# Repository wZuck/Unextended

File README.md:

# Unextended keyboard

> Wireless NIZ development A2: [English](docs/direct-usb-A2.md) · [简体中文](docs/direct-usb-A2.zh-CN.md). ANSI 61 / BLE + USB; native nice!nano USB-C directly at the case opening, with a separate low-level carrier and revised internal V1 pocket. Not fabrication-ready. [Renders](docs/renders.md) · [Website source](website/README.md). Original ALPS project documentation follows.

Welcome to the **Unextended Keyboard** project. A 60% keyboard that targets ALPS switches and specifically the keycaps from Apple Extended Keyboards.

## Disclaimer:
I am not a case designer, this is just a personal project for me to play with 3D CAD. There are likely many best practices that are missing in this project and there are likely many improvements that can be made for better machinability. See this as a work in progress or something to get inspiration from, rather than something production ready.

**If you get these produced in PC, make sure to use threaded insers for the screws.**

## Status:
A V1 prototype has been made by PCBWay of the current V1-step model and a full wireless build have been made with a Cyber60 PCB. A mini-GB has been completed using the FE-step model by Gaoije in both PC and Aluminium and a full wired build have been made with a AEKISO60. For wireless builds I recommend the V1-model and Cyber 60 PCB. For wired builds I recommend the FE-model and either the Waffling60 Alps or the AEKISO60. MX builds can also be used in both V1 and FE cases.

I have also done a slimmer version, called Unextended Standard. This version is designed for use with M0116 or M0118 keycaps and the Unextended Standard PCB: https://github.com/4pplet/Unextended-Standard-PCB. Note: The "Standard" version of the case and PCB is not 60%. For a 60% build, use the Unextended V1 or Unextended FE and a 60% PCB (like the waffling60 alps or aekiso60).

## Keyboard Parts:
- Case
- PCB + C1 or C3 compatible daughterboard
- 3.7v single cell lipo/liion battery with a 2-pin JST PH connector (check polarity on PCB) if wireless.
- Plate
- SKUF feet
- O-ring (OD 3.5-3.55MM, Length 175-185mm)
- Cover plate for battery and daughterboard (0.6mm FR4 was used for the protos) for V1, not strictly needed.
- M2 screws for daughter board and cover plate.
- Alps switches, stabs and AEK-keycaps
- 3.7V LiPo Battery (a 3mm thick, 303759 750mAh battery was used for protos: https://www.aliexpress.com/item/33019120350.html) if wireless.

## Specs:
- V1 and FE: 60%, Standard: 55%
- Bakeneko V3 rubber worm/o-ring mount
- Compatible projects: 
  - Unextended V1 and Unextended FE: Cyber60, Waffling60 and AEKISO60 (USB-port need to be unmounted or desoldered to fit)
  - Unextended Standard FE: Unextended Standard PCB
- 5.4 degree typing angle

## Revisions:
- P1: 2021-09-20 - 3D printed concept with a bit wider bezels
- P2: 2021-11-18 - Alu CNC proto from PCB way. Slimmed down bezels and added battery cover.
- V1: 2022-01-23 - Second prototype of the case. Changed to V3 Bakeneko mounting posts and recessed and moved down the daughterboard slightly. PCBWay had issues tapping the screw holes closest to the edge for the daugheter board in P2.
- FE V1: 2022-09-17 - Reworked case by Laminar, adding a weight and removing channel for battery. This version is not intended for use with a internal battery.
- FE Standard V1: 2022-12-16 - Reworking the case to a slimmer version intended for M0116, M0118, NeXT and IIc keycaps.

## Initial 3D proto (P1):
SLA print from PCBWay
3d_print

## Initial alu proto (P2):
CNCd ALU from PCBWay

## Pics of mini GB of Unextended FE:
CNCd PC from Gaojie

## Initial proto of Unextended Standard:
Modified release for use of M0118 and M0116 keycaps. SLA Print from Gaoije, print from PCBWay also made.

<a href='https://ko-fi.com/4pplet' target='_blank'>

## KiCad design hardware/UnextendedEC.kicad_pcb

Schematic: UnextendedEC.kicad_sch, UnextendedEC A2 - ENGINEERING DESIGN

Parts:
C1, C2, C3: 100n; C_0805_2012Metric_Pad1.18x1.45mm_HandSolder
C4: 220p_C0G; C_0805_2012Metric_Pad1.18x1.45mm_HandSolder
C5: 1u; C_0805_2012Metric_Pad1.18x1.45mm_HandSolder
EC1: Esc; ecs_pad_1U_no_ring
EC2: 1; ecs_pad_1U_no_ring
EC3: 2; ecs_pad_1U_no_ring
EC4: 3; ecs_pad_1U_no_ring
EC5: 4; ecs_pad_1U_no_ring
EC6: 5; ecs_pad_1U_no_ring
EC7: 6; ecs_pad_1U_no_ring
EC8: 7; ecs_pad_1U_no_ring
EC9: 8; ecs_pad_1U_no_ring
EC10: 9; ecs_pad_1U_no_ring
EC11: 0; ecs_pad_1U_no_ring
EC12: -; ecs_pad_1U_no_ring
EC13: =; ecs_pad_1U_no_ring
EC14: Backspace; ecs_pad_1U_no_ring
EC15: Tab; ecs_pad_1U_no_ring
EC16: Q; ecs_pad_1U_no_ring
EC17: W; ecs_pad_1U_no_ring
EC18: E; ecs_pad_1U_no_ring
EC19: R; ecs_pad_1U_no_ring
EC20: T; ecs_pad_1U_no_ring
EC21: Y; ecs_pad_1U_no_ring
EC22: U; ecs_pad_1U_no_ring
EC23: I; ecs_pad_1U_no_ring
EC24: O; ecs_pad_1U_no_ring
EC25: P; ecs_pad_1U_no_ring
EC26: [; ecs_pad_1U_no_ring
EC27: ]; ecs_pad_1U_no_ring
EC28: \; ecs_pad_1U_no_ring
EC29: Caps; ecs_pad_1U_no_ring
EC30: A; ecs_pad_1U_no_ring
EC31: S; ecs_pad_1U_no_ring
EC32: D; ecs_pad_1U_no_ring
EC33: F; ecs_pad_1U_no_ring
EC34: G; ecs_pad_1U_no_ring
EC35: H; ecs_pad_1U_no_ring
EC36: J; ecs_pad_1U_no_ring
EC37: K; ecs_pad_1U_no_ring
EC38: L; ecs_pad_1U_no_ring
EC39: ;; ecs_pad_1U_no_ring
EC40: '; ecs_pad_1U_no_ring
EC41: Enter; ecs_pad_1U_no_ring
EC42: Shift; ecs_pad_1U_no_ring
EC43: Z; ecs_pad_1U_no_ring
EC44: X; ecs_pad_1U_no_ring
EC45: C; ecs_pad_1U_no_ring
EC46: V; ecs_pad_1U_no_ring
EC47: B; ecs_pad_1U_no_ring
EC48: N; ecs_pad_1U_no_ring
EC49: M; ecs_pad_1U_no_ring
EC50: ,; ecs_pad_1U_no_ring
EC51: .; ecs_pad_1U_no_ring
EC52: /; ecs_pad_1U_no_ring
EC53: RShift; ecs_pad_1U_no_ring
EC54: LCTRL; ecs_pad_1U_no_ring
EC55: LGUI; ecs_pad_1U_no_ring
EC56: LAlt; ecs_pad_1U_no_ring
EC57: Space; ecs_pad_1U_no_ring
EC58: RAlt; ecs_pad_1U_no_ring
EC59: Fn; ecs_pad_1U_no_ring
EC60: Menu; ecs_pad_1U_no_ring
EC61: RCTRL; ecs_pad_1U_no_ring
J1: JST_S2B-PH-K; Battery_PH2
J2: FH12-24S-0.5SH; Hirose_FH12-24S-0.5SH_1x24-1MP_P0.50mm_Horizontal
Q1: AO3401A; SOT-23
R1, R2, R3, R4, R5: 100; R_0805_2012Metric_Pad1.20x1.40mm_HandSolder
R10, R11, R12, R13, R14, R15, R16, R17, R18, R19, R20, R21, R22, R23, R24, R30, R33, R34, R35: 100k; R_0805_2012Metric_Pad1.20x1.40mm_HandSolder
R31, R32, R36: 1k; R_0805_2012Metric_Pad1.20x1.40mm_HandSolder
R37: 47; R_0805_2012Metric_Pad1.20x1.40mm_HandSolder
SW1: Battery_switch_pigtail; SPST_PIGTAIL_2.54
SW2: Reset_NO; RESET_2.54_TH
U2, U3: CD74HC4051M96; SOIC-16_3.9x9.9mm_P1.27mm
U4: OPA350UA; SOIC-8_3.9x4.9mm_P1.27mm

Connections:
ADC: J2.20 (ADC), R37.2 (ADC)
AFE_3V3: C3.1 (AFE_3V3), Q1.3 (D), U4.7 (V+)
AFE_GATE: Q1.1 (G), R35.1 (AFE_GATE), R36.2 (AFE_GATE)
AFE_ON_N: J2.18 (AFE_ON_N), R36.1 (AFE_ON_N)
AMP_OUT: R30.1 (AMP_OUT), R37.1 (AMP_OUT), U4.6 (OUT)
BAT_RAW: J1.1 (BAT_RAW), SW1.1 (BAT_RAW)
BAT_SW: J2.22 (BAT_SW), SW1.2 (BAT_SW)
COL0: EC1.2 (SENSE), EC15.2 (SENSE), EC29.2 (SENSE), EC54.2 (SENSE), R10.1 (COL0), U2.13 (X0)
COL1: EC2.2 (SENSE), EC42.2 (SENSE), EC55.2 (SENSE), R11.1 (COL1), U2.14 (X1)
COL2: EC3.2 (SENSE), EC16.2 (SENSE), EC30.2 (SENSE), EC43.2 (SENSE), R12.1 (COL2), U2.15 (X2)
COL3: EC4.2 (SENSE), EC17.2 (SENSE), EC31.2 (SENSE), EC44.2 (SENSE), EC56.2 (SENSE), R13.1 (COL3), U2.12 (X3)
COL4: EC5.2 (SENSE), EC18.2 (SENSE), EC32.2 (SENSE), EC45.2 (SENSE), R14.1 (COL4), U2.1 (X4)
COL5: EC6.2 (SENSE), EC19.2 (SENSE), EC33.2 (SENSE), EC46.2 (SENSE), R15.1 (COL5), U2.5 (X5)
COL6: EC7.2 (SENSE), EC20.2 (SENSE), EC34.2 (SENSE), EC47.2 (SENSE), EC57.2 (SENSE), R16.1 (COL6), U2.2 (X6)
COL7: EC8.2 (SENSE), EC21.2 (SENSE), EC35.2 (SENSE), EC48.2 (SENSE), R17.1 (COL7), U2.4 (X7)
COL8: EC9.2 (SENSE), EC22.2 (SENSE), EC36.2 (SENSE), EC49.2 (SENSE), R18.1 (COL8), U3.13 (X0)
COL9: EC10.2 (SENSE), EC23.2 (SENSE), EC37.2 (SENSE), EC50.2 (SENSE), R19.1 (COL9), U3.14 (X1)
COL10: EC11.2 (SENSE), EC24.2 (SENSE), EC38.2 (SENSE), EC51.2 (SENSE), EC58.2 (SENSE), R20.1 (COL10), U3.15 (X2)
COL11: EC12.2 (SENSE), EC25.2 (SENSE), EC39.2 (SENSE), EC52.2 (SENSE), EC59.2 (SENSE), R21.1 (COL11), U3.12 (X3)
COL12: EC13.2 (SENSE), EC26.2 (SENSE), EC40.2 (SENSE), R22.1 (COL12), U3.1 (X4)
COL13: EC27.2 (SENSE), EC41.2 (SENSE), EC53.2 (SENSE), EC60.2 (SENSE), R23.1 (COL13), U3.5 (X5)
COL14: EC14.2 (SENSE), EC28.2 (SENSE), EC61.2 (SENSE), R24.1 (COL14), U3.2 (X6)
DRAIN: J2.17 (DRAIN), R32.1 (DRAIN)
FB: R30.2 (FB), R31.1 (FB), U4.2 (IN-)
GND: C1.2 (GND), C2.2 (GND), C3.2 (GND), C4.2 (GND), C5.2 (GND), EC1.3 (GUARD), EC2.3 (GUARD), EC3.3 (GUARD), EC4.3 (GUARD), EC5.3 (GUARD), EC6.3 (GUARD), EC7.3 (GUARD), EC8.3 (GUARD), EC9.3 (GUARD), EC10.3 (GUARD), EC11.3 (GUARD), EC12.3 (GUARD), EC13.3 (GUARD), EC14.3 (GUARD), EC15.3 (GUARD), EC16.3 (GUARD), EC17.3 (GUARD), EC18.3 (GUARD), EC19.3 (GUARD), EC20.3 (GUARD), EC21.3 (GUARD), EC22.3 (GUARD), EC23.3 (GUARD), EC24.3 (GUARD), EC25.3 (GUARD), EC26.3 (GUARD), EC27.3 (GUARD), EC28.3 (GUARD), EC29.3 (GUARD), EC30.3 (GUARD), EC31.3 (GUARD), EC32.3 (GUARD), EC33.3 (GUARD), EC34.3 (GUARD), EC35.3 (GUARD), EC36.3 (GUARD), EC37.3 (GUARD), EC38.3 (GUARD), EC39.3 (GUARD), EC40.3 (GUARD), EC41.3 (GUARD), EC42.3 (GUARD), EC43.3 (GUARD), EC44.3 (GUARD), EC45.3 (GUARD), EC46.3 (GUARD), EC47.3 (GUARD), EC48.3 (GUARD), EC49.3 (GUARD), EC50.3 (GUARD), EC51.3 (GUARD), EC52.3 (GUARD), EC53.3 (GUARD), EC54.3 (GUARD), EC55.3 (GUARD), EC56.3 (GUARD), EC57.3 (GUARD), EC58.3 (GUARD), EC59.3 (GUARD), EC60.3 (GUARD), EC61.3 (GUARD), J1.2 (GND), J2.1 (GND), J2.2 (GND), J2.4 (GND), J2.10 (GND), J2.16 (GND), J2.19 (GND), J2.21 (GND), J2.24 (GND), R10.2 (GND), R11.2 (GND), R12.2 (GND), R13.2 (GND), R14.2 (GND), R15.2 (GND), R16.2 (GND), R17.2 (GND), R18.2 (GND), R19.2 (GND), R20.2 (GND), R21.2 (GND), R22.2 (GND), R23.2 (GND), R24.2 (GND), R31.2 (GND), SW2.2 (GND), U2.7 (VEE), U2.8 (GND), U3.4 (X7), U3.7 (VEE), U3.8 (GND), U4.4 (V-)
MUX0_INH: J2.14 (MUX0_INH), R33.1 (MUX0_INH), U2.6 (INH)
MUX1_INH: J2.15 (MUX1_INH), R34.1 (MUX1_INH), U3.6 (INH)
MUX_A: J2.11 (MUX_A), U2.11 (A), U3.11 (A)
MUX_B: J2.12 (MUX_B), U2.10 (B), U3.10 (B)
MUX_C: J2.13 (MUX_C), U2.9 (C), U3.9 (C)
RESET: J2.23 (RESET), SW2.1 (RESET)
ROW0: EC1.1 (DRIVE), EC2.1 (DRIVE), EC3.1 (DRIVE), EC4.1 (DRIVE), EC5.1 (DRIVE), EC6.1 (DRIVE), EC7.1 (DRIVE), EC8.1 (DRIVE), EC9.1 (DRIVE), EC10.1 (DRIVE), EC11.1 (DRIVE), EC12.1 (DRIVE), EC13.1 (DRIVE), EC14.1 (DRIVE), R1.2 (ROW0)
ROW1: EC15.1 (DRIVE), EC16.1 (DRIVE), EC17.1 (DRIVE), EC18.1 (DRIVE), EC19.1 (DRIVE), EC20.1 (DRIVE), EC21.1 (DRIVE), EC22.1 (DRIVE), EC23.1 (DRIVE), EC24.1 (DRIVE), EC25.1 (DRIVE), EC26.1 (DRIVE), EC27.1 (DRIVE), EC28.1 (DRIVE), R2.2 (ROW1)
ROW2: EC29.1 (DRIVE), EC30.1 (DRIVE), EC31.1 (DRIVE), EC32.1 (DRIVE), EC33.1 (DRIVE), EC34.1 (DRIVE), EC35.1 (DRIVE), EC36.1 (DRIVE), EC37.1 (DRIVE), EC38.1 (DRIVE), EC39.1 (DRIVE), EC40.1 (DRIVE), EC41.1 (DRIVE), R3.2 (ROW2)
ROW3: EC42.1 (DRIVE), EC43.1 (DRIVE), EC44.1 (DRIVE), EC45.1 (DRIVE), EC46.1 (DRIVE), EC47.1 (DRIVE), EC48.1 (DRIVE), EC49.1 (DRIVE), EC50.1 (DRIVE), EC51.1 (DRIVE), EC52.1 (DRIVE), EC53.1 (DRIVE), R4.2 (ROW3)
ROW4: EC54.1 (DRIVE), EC55.1 (DRIVE), EC56.1 (DRIVE), EC57.1 (DRIVE), EC58.1 (DRIVE), EC59.1 (DRIVE), EC60.1 (DRIVE), EC61.1 (DRIVE), R5.2 (ROW4)
ROW_DRV0: J2.5 (ROW_DRV0), R1.1 (ROW_DRV0)
ROW_DRV1: J2.6 (ROW_DRV1), R2.1 (ROW_DRV1)
ROW_DRV2: J2.7 (ROW_DRV2), R3.1 (ROW_DRV2)
ROW_DRV3: J2.8 (ROW_DRV3), R4.1 (ROW_DRV3)
ROW_DRV4: J2.9 (ROW_DRV4), R5.1 (ROW_DRV4)
SENSE: C4.1 (SENSE), R32.2 (SENSE), U2.3 (COM), U3.3 (COM), U4.3 (IN+)
VCC: C1.1 (VCC), C2.1 (VCC), C5.1 (VCC), J2.3 (VCC), Q1.2 (S), R33.2 (VCC), R34.2 (VCC), R35.2 (VCC), U2.16 (VCC), U3.16 (VCC)

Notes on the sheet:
UnextendedEC A2 | NiZ EC + ANSI 6.25u + nice!nano v2 | ENGINEERING PROTOTYPE
Native nice!nano USB-C is the external port. J2 carries no USB, VBUS or high-impedance SENSE.
U2/U3: only one INH low at a time. U4 gain 101. DRAIN goes through R32 to SENSE. Q1 gates U4 only.
SW1/SW2 are 2.54mm solder-hole harnesses. No external 5V connection to U1 BATTERY+.
EC electrodes: logical row = physical row; column = floor(x_u + width_u/2), including empty column bins.

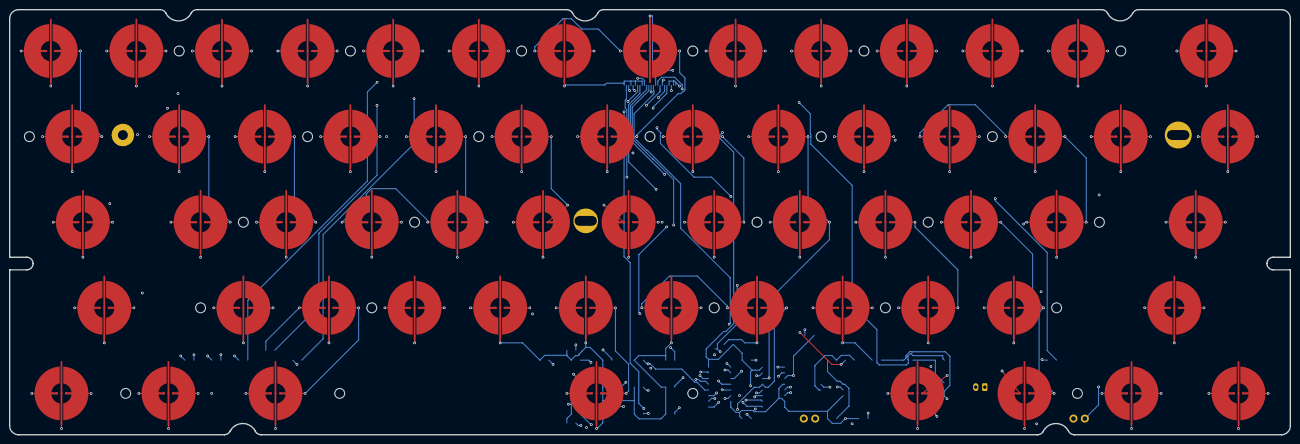
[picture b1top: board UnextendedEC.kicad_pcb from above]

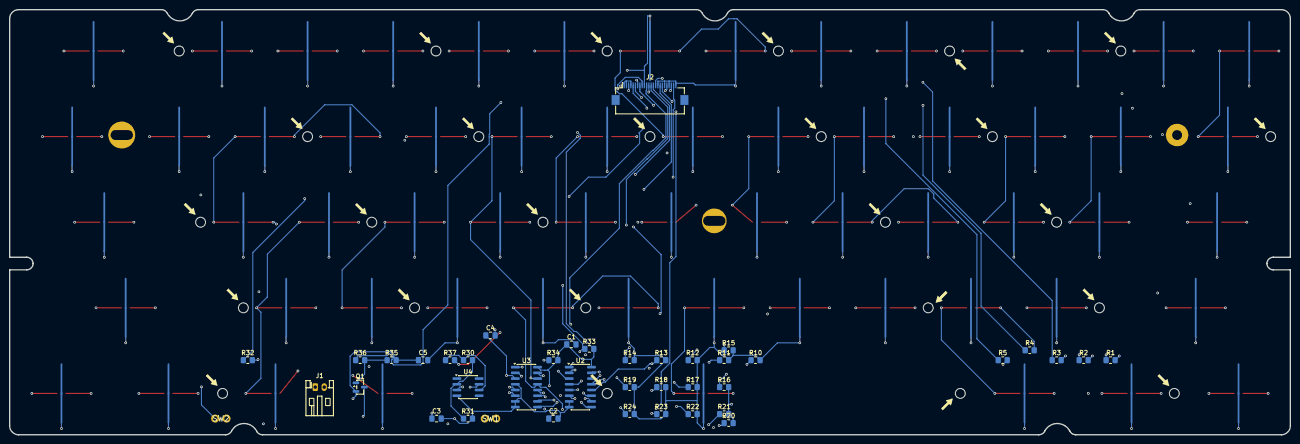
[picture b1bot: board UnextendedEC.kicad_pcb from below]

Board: 4 copper layers, 285.0 x 94.6 mm, 128 parts (41 on the bottom side), 43 nets.

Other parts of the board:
H1, H2, H3, H4, H5, H6, H7, H8, H9, H10, H11, H12, H13, H14, H15, H16, H17, H18, H19, H20, H21, H22, H23, H24, H25, H26: MountingHole; HOLE_M2

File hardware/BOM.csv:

Reference,Value,Footprint,Side,X_mm,Y_mm
J2,FH12-24S-0.5SH,Connector_FFC-FPC:Hirose_FH12-24S-0.5SH_1x24-1MP_P0.50mm_Horizontal,B,142.5,18.7
U2,CD74HC4051M96,Package_SO:SOIC-16_3.9x9.9mm_P1.27mm,B,158,84
U3,CD74HC4051M96,Package_SO:SOIC-16_3.9x9.9mm_P1.27mm,B,170,84
U4,OPA350UA,Package_SO:SOIC-8_3.9x4.9mm_P1.27mm,B,183,84
Q1,AO3401A,Package_TO_SOT_SMD:SOT-23,B,207,84
R1,100,Resistor_SMD:R_0805_2012Metric_Pad1.20x1.40mm_HandSolder,B,40,78
R2,100,Resistor_SMD:R_0805_2012Metric_Pad1.20x1.40mm_HandSolder,B,46,78
R3,100,Resistor_SMD:R_0805_2012Metric_Pad1.20x1.40mm_HandSolder,B,52,78
R4,100,Resistor_SMD:R_0805_2012Metric_Pad1.20x1.40mm_HandSolder,B,58,75.8
R5,100,Resistor_SMD:R_0805_2012Metric_Pad1.20x1.40mm_HandSolder,B,64,78
R10,100k,Resistor_SMD:R_0805_2012Metric_Pad1.20x1.40mm_HandSolder,B,119,78
R11,100k,Resistor_SMD:R_0805_2012Metric_Pad1.20x1.40mm_HandSolder,B,126,78
R12,100k,Resistor_SMD:R_0805_2012Metric_Pad1.20x1.40mm_HandSolder,B,133,78
R13,100k,Resistor_SMD:R_0805_2012Metric_Pad1.20x1.40mm_HandSolder,B,140,78
R14,100k,Resistor_SMD:R_0805_2012Metric_Pad1.20x1.40mm_HandSolder,B,147,78
R15,100k,Resistor_SMD:R_0805_2012Metric_Pad1.20x1.40mm_HandSolder,B,125,75.8
R16,100k,Resistor_SMD:R_0805_2012Metric_Pad1.20x1.40mm_HandSolder,B,126,84
R17,100k,Resistor_SMD:R_0805_2012Metric_Pad1.20x1.40mm_HandSolder,B,133,84
R18,100k,Resistor_SMD:R_0805_2012Metric_Pad1.20x1.40mm_HandSolder,B,140,84
R19,100k,Resistor_SMD:R_0805_2012Metric_Pad1.20x1.40mm_HandSolder,B,147,84
R20,100k,Resistor_SMD:R_0805_2012Metric_Pad1.20x1.40mm_HandSolder,B,125,92
R21,100k,Resistor_SMD:R_0805_2012Metric_Pad1.20x1.40mm_HandSolder,B,126,90
R22,100k,Resistor_SMD:R_0805_2012Metric_Pad1.20x1.40mm_HandSolder,B,133,90
R23,100k,Resistor_SMD:R_0805_2012Metric_Pad1.20x1.40mm_HandSolder,B,140,90
R24,100k,Resistor_SMD:R_0805_2012Metric_Pad1.20x1.40mm_HandSolder,B,147,90
R30,100k,Resistor_SMD:R_0805_2012Metric_Pad1.20x1.40mm_HandSolder,B,183,78
R31,1k,Resistor_SMD:R_0805_2012Metric_Pad1.20x1.40mm_HandSolder,B,183,91
R32,1k,Resistor_SMD:R_0805_2012Metric_Pad1.20x1.40mm_HandSolder,B,232,78
R33,100k,Resistor_SMD:R_0805_2012Metric_Pad1.20x1.40mm_HandSolder,B,156,75.5
R34,100k,Resistor_SMD:R_0805_2012Metric_Pad1.20x1.40mm_HandSolder,B,164,78
R35,100k,Resistor_SMD:R_0805_2012Metric_Pad1.20x1.40mm_HandSolder,B,200,78
R36,1k,Resistor_SMD:R_0805_2012Metric_Pad1.20x1.40mm_HandSolder,B,207,78
R37,47,Resistor_SMD:R_0805_2012Metric_Pad1.20x1.40mm_HandSolder,B,187,78
C1,100n,Capacitor_SMD:C_0805_2012Metric_Pad1.18x1.45mm_HandSolder,B,160,74.5
C2,100n,Capacitor_SMD:C_0805_2012Metric_Pad1.18x1.45mm_HandSolder,B,164,91
C3,100n,Capacitor_SMD:C_0805_2012Metric_Pad1.18x1.45mm_HandSolder,B,190,91
C4,220p_C0G,Capacitor_SMD:C_0805_2012Metric_Pad1.18x1.45mm_HandSolder,B,178,72.5
C5,1u,Capacitor_SMD:C_0805_2012Metric_Pad1.18x1.45mm_HandSolder,B,193,78
J1,JST_S2B-PH-K,UnextendedEC:Battery_PH2,B,217,84
SW1,Battery_switch_pigtail,UnextendedEC:SPST_PIGTAIL_2.54,B,178,91
SW2,Reset_NO,UnextendedEC:RESET_2.54_TH,B,238,91
EC1,Esc,UnextendedEC:ecs_pad_1U_no_ring,F,9.15,9.2
EC2,1,UnextendedEC:ecs_pad_1U_no_ring,F,28.200000000000003,9.2
EC3,2,UnextendedEC:ecs_pad_1U_no_ring,F,47.25,9.2
EC4,3,UnextendedEC:ecs_pad_1U_no_ring,F,66.30000000000001,9.2
EC5,4,UnextendedEC:ecs_pad_1U_no_ring,F,85.35000000000001,9.2
EC6,5,UnextendedEC:ecs_pad_1U_no_ring,F,104.4,9.2
EC7,6,UnextendedEC:ecs_pad_1U_no_ring,F,123.45000000000002,9.2
EC8,7,UnextendedEC:ecs_pad_1U_no_ring,F,142.5,9.2
EC9,8,UnextendedEC:ecs_pad_1U_no_ring,F,161.55,9.2
EC10,9,UnextendedEC:ecs_pad_1U_no_ring,F,180.60000000000002,9.2
EC11,0,UnextendedEC:ecs_pad_1U_no_ring,F,199.65,9.2
EC12,-,UnextendedEC:ecs_pad_1U_no_ring,F,218.70000000000002,9.2
EC13,=,UnextendedEC:ecs_pad_1U_no_ring,F,237.75000000000003,9.2
EC14,Backspace,UnextendedEC:ecs_pad_1U_no_ring,F,266.325,9.2
EC15,Tab,UnextendedEC:ecs_pad_1U_no_ring,F,13.912500000000001,28.25
EC16,Q,UnextendedEC:ecs_pad_1U_no_ring,F,37.725,28.25
EC17,W,UnextendedEC:ecs_pad_1U_no_ring,F,56.775,28.25
EC18,E,UnextendedEC:ecs_pad_1U_no_ring,F,75.825,28.25
EC19,R,UnextendedEC:ecs_pad_1U_no_ring,F,94.87500000000001,28.25
EC20,T,UnextendedEC:ecs_pad_1U_no_ring,F,113.92500000000001,28.25
EC21,Y,UnextendedEC:ecs_pad_1U_no_ring,F,132.975,28.25
EC22,U,UnextendedEC:ecs_pad_1U_no_ring,F,152.025,28.25
EC23,I,UnextendedEC:ecs_pad_1U_no_ring,F,171.07500000000002,28.25
EC24,O,UnextendedEC:ecs_pad_1U_no_ring,F,190.125,28.25
EC25,P,UnextendedEC:ecs_pad_1U_no_ring,F,209.175,28.25
EC26,[,UnextendedEC:ecs_pad_1U_no_ring,F,228.22500000000002,28.25
EC27,],UnextendedEC:ecs_pad_1U_no_ring,F,247.275,28.25
EC28,\,UnextendedEC:ecs_pad_1U_no_ring,F,271.0875,28.25
EC29,Caps,UnextendedEC:ecs_pad_1U_no_ring,F,16.293750000000003,47.3
EC30,A,UnextendedEC:ecs_pad_1U_no_ring,F,42.4875,47.3
EC31,S,UnextendedEC:ecs_pad_1U_no_ring,F,61.5375,47.3
EC32,D,UnextendedEC:ecs_pad_1U_no_ring,F,80.5875,47.3
EC33,F,UnextendedEC:ecs_pad_1U_no_ring,F,99.6375,47.3
EC34,G,UnextendedEC:ecs_pad_1U_no_ring,F,118.68750000000001,47.3
EC35,H,UnextendedEC:ecs_pad_1U_no_ring,F,137.7375,47.3
EC36,J,UnextendedEC:ecs_pad_1U_no_ring,F,156.78750000000002,47.3
EC37,K,UnextendedEC:ecs_pad_1U_no_ring,F,175.8375,47.3
EC38,L,UnextendedEC:ecs_pad_1U_no_ring,F,194.88750000000002,47.3
EC39,;,UnextendedEC:ecs_pad_1U_no_ring,F,213.9375,47.3
EC40,',UnextendedEC:ecs_pad_1U_no_ring,F,232.9875,47.3
EC41,Enter,UnextendedEC:ecs_pad_1U_no_ring,F,263.94375,47.3
EC42,Shift,UnextendedEC:ecs_pad_1U_no_ring,F,21.05625,66.35000000000001
EC43,Z,UnextendedEC:ecs_pad_1U_no_ring,F,52.0125,66.35000000000001
EC44,X,UnextendedEC:ecs_pad_1U_no_ring,F,71.0625,66.35000000000001
EC45,C,UnextendedEC:ecs_pad_1U_no_ring,F,90.11250000000001,66.35000000000001
EC46,V,UnextendedEC:ecs_pad_1U_no_ring,F,109.16250000000001,66.35000000000001
EC47,B,UnextendedEC:ecs_pad_1U_no_ring,F,128.2125,66.35000000000001
EC48,N,UnextendedEC:ecs_pad_1U_no_ring,F,147.26250000000002,66.35000000000001
EC49,M,UnextendedEC:ecs_pad_1U_no_ring,F,166.3125,66.35000000000001
EC50,",",UnextendedEC:ecs_pad_1U_no_ring,F,185.3625,66.35000000000001
EC51,.,UnextendedEC:ecs_pad_1U_no_ring,F,204.41250000000002,66.35000000000001
EC52,/,UnextendedEC:ecs_pad_1U_no_ring,F,223.4625,66.35000000000001
EC53,RShift,UnextendedEC:ecs_pad_1U_no_ring,F,259.18125,66.35000000000001
EC54,LCTRL,UnextendedEC:ecs_pad_1U_no_ring,F,11.53125,85.4
EC55,LGUI,UnextendedEC:ecs_pad_1U_no_ring,F,35.34375,85.4
EC56,LAlt,UnextendedEC:ecs_pad_1U_no_ring,F,59.15625,85.4
EC57,Space,UnextendedEC:ecs_pad_1U_no_ring,F,130.59375,85.4
EC58,RAlt,UnextendedEC:ecs_pad_1U_no_ring,F,202.03125,85.4
EC59,Fn,UnextendedEC:ecs_pad_1U_no_ring,F,225.84375,85.4
EC60,Menu,UnextendedEC:ecs_pad_1U_no_ring,F,249.65625000000003,85.4
EC61,RCTRL,UnextendedEC:ecs_pad_1U_no_ring,F,273.46875,85.4

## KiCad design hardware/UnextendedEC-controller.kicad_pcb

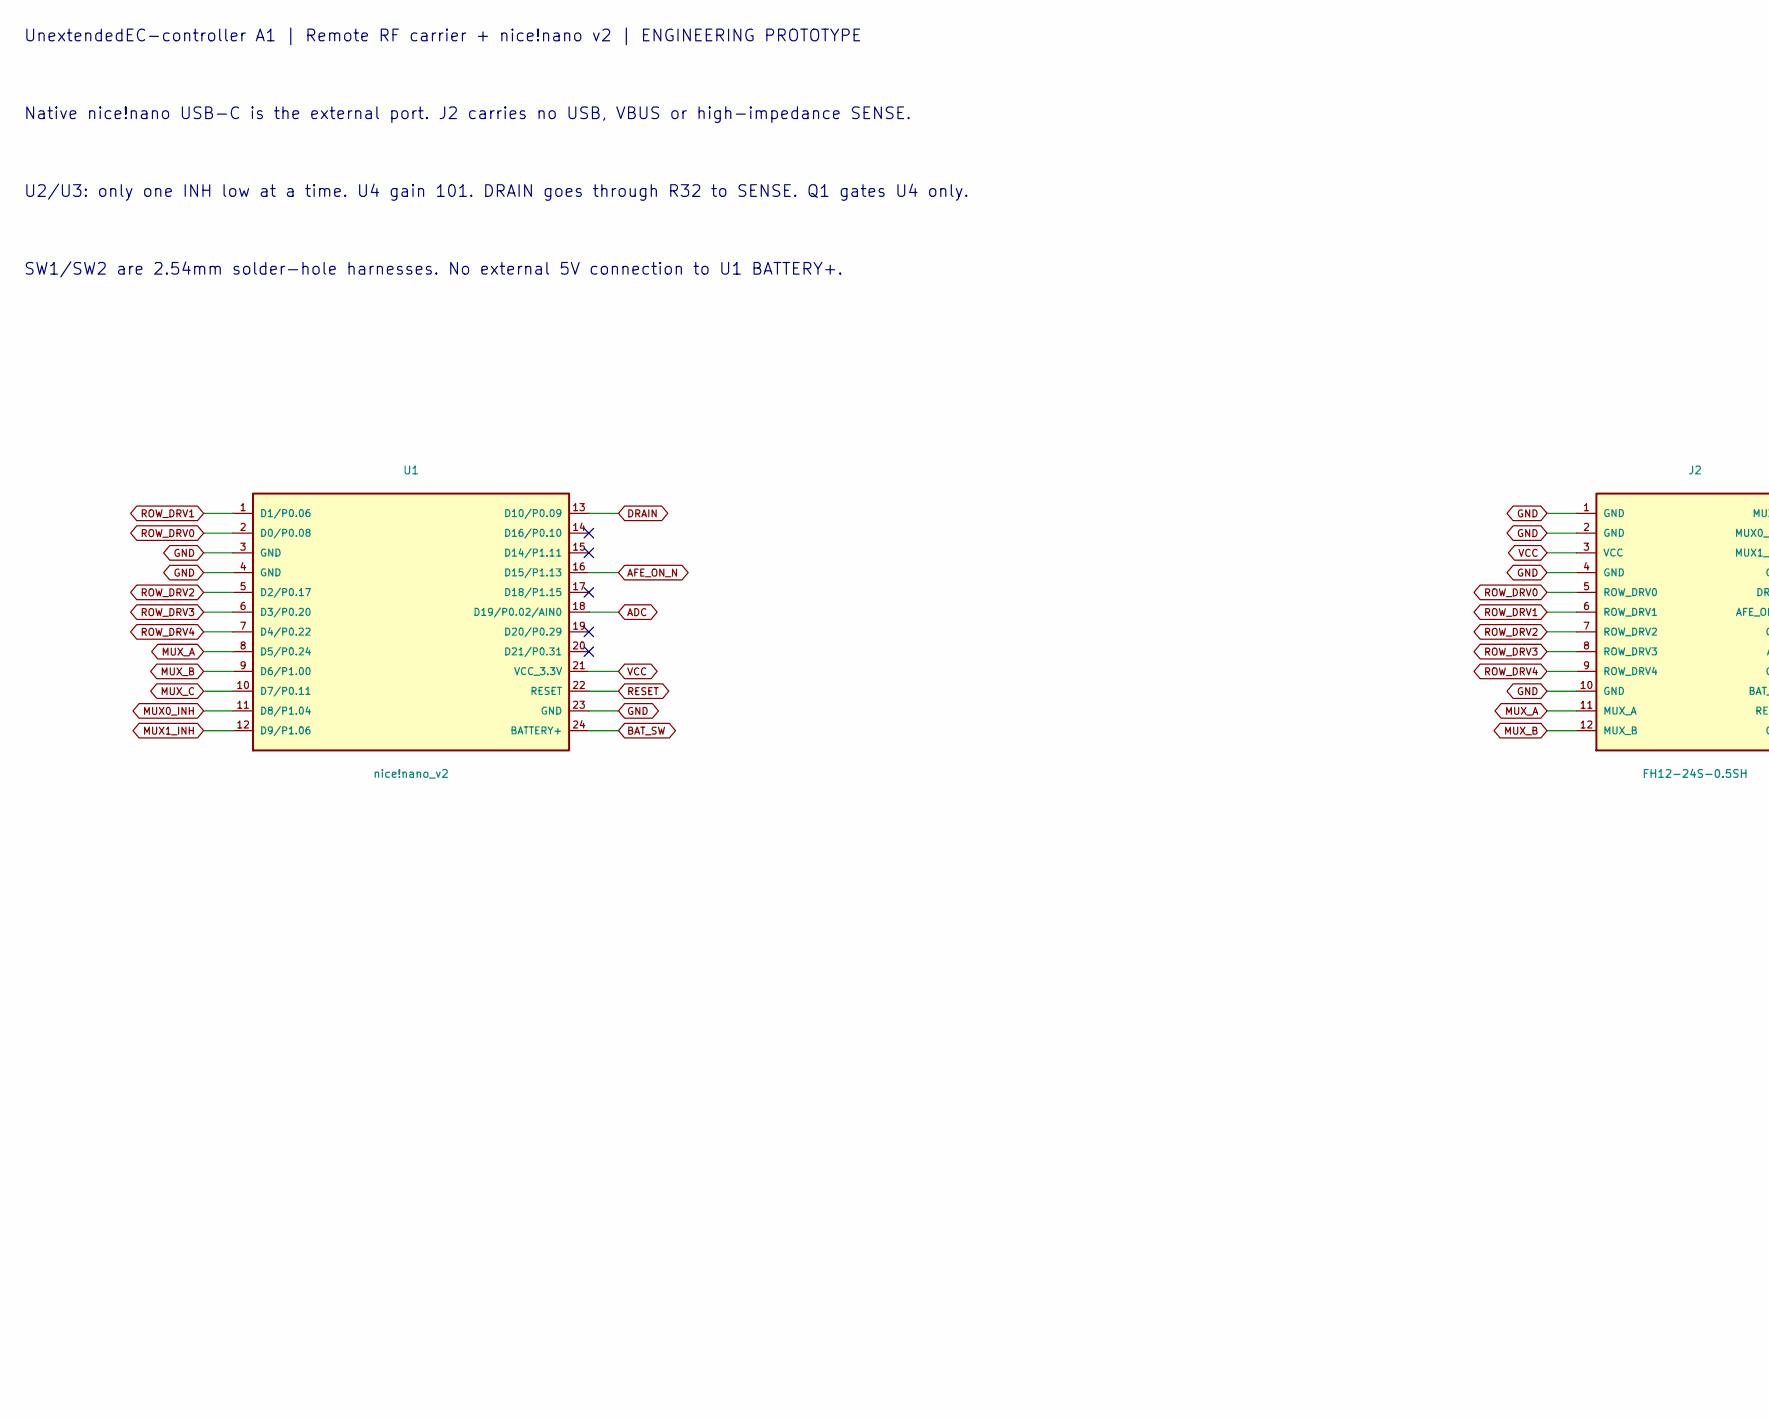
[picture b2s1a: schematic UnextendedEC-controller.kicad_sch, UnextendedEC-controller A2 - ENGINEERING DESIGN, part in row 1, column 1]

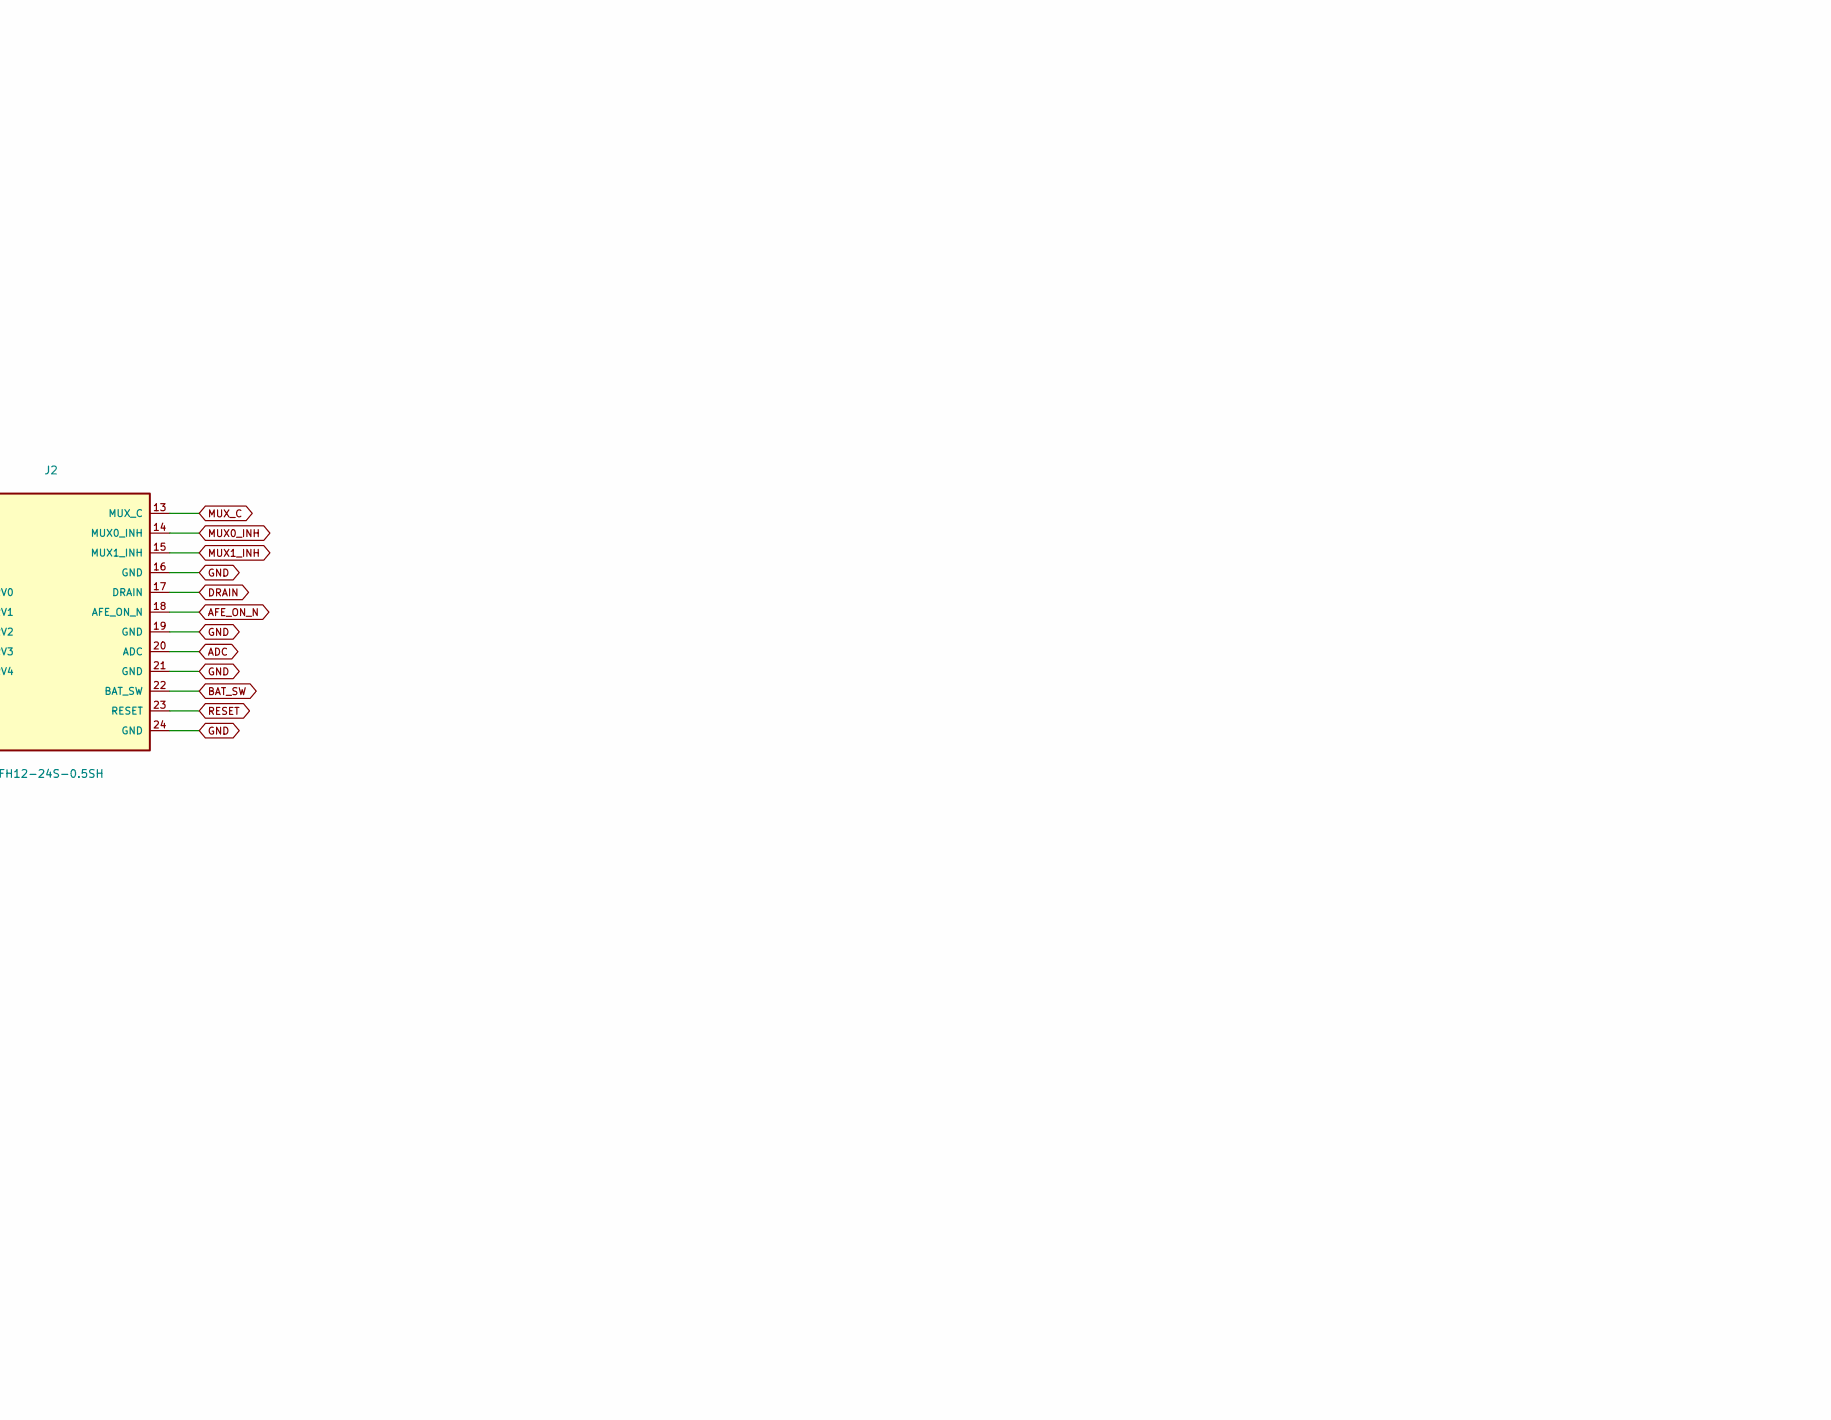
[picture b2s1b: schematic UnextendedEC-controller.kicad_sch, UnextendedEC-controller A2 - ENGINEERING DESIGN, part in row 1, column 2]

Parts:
C6: 1n_C0G; C_0805_2012Metric_Pad1.18x1.45mm_HandSolder
J2: FH12-24S-0.5SH; Hirose_FH12-24S-0.5SH_1x24-1MP_P0.50mm_Horizontal
U1: nice!nano_v2; nice_nano

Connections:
ADC: C6.1 (ADC), J2.20 (ADC), U1.18 (D19/P0.02/AIN0)
AFE_ON_N: J2.18 (AFE_ON_N), U1.16 (D15/P1.13)
BAT_SW: J2.22 (BAT_SW), U1.24 (BATTERY+)
DRAIN: J2.17 (DRAIN), U1.13 (D10/P0.09)
GND: C6.2 (GND), J2.1 (GND), J2.2 (GND), J2.4 (GND), J2.10 (GND), J2.16 (GND), J2.19 (GND), J2.21 (GND), J2.24 (GND), U1.3 (GND), U1.4 (GND), U1.23 (GND)
MUX0_INH: J2.14 (MUX0_INH), U1.11 (D8/P1.04)
MUX1_INH: J2.15 (MUX1_INH), U1.12 (D9/P1.06)
MUX_A: J2.11 (MUX_A), U1.8 (D5/P0.24)
MUX_B: J2.12 (MUX_B), U1.9 (D6/P1.00)
MUX_C: J2.13 (MUX_C), U1.10 (D7/P0.11)
RESET: J2.23 (RESET), U1.22 (RESET)
ROW_DRV0: J2.5 (ROW_DRV0), U1.2 (D0/P0.08)
ROW_DRV1: J2.6 (ROW_DRV1), U1.1 (D1/P0.06)
ROW_DRV2: J2.7 (ROW_DRV2), U1.5 (D2/P0.17)
ROW_DRV3: J2.8 (ROW_DRV3), U1.6 (D3/P0.20)
ROW_DRV4: J2.9 (ROW_DRV4), U1.7 (D4/P0.22)
VCC: J2.3 (VCC), U1.21 (VCC_3.3V)

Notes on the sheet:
UnextendedEC-controller A1 | Remote RF carrier + nice!nano v2 | ENGINEERING PROTOTYPE
Native nice!nano USB-C is the external port. J2 carries no USB, VBUS or high-impedance SENSE.
U2/U3: only one INH low at a time. U4 gain 101. DRAIN goes through R32 to SENSE. Q1 gates U4 only.
SW1/SW2 are 2.54mm solder-hole harnesses. No external 5V connection to U1 BATTERY+.
EC electrodes: logical row = physical row; column = floor(x_u + width_u/2), including empty column bins.

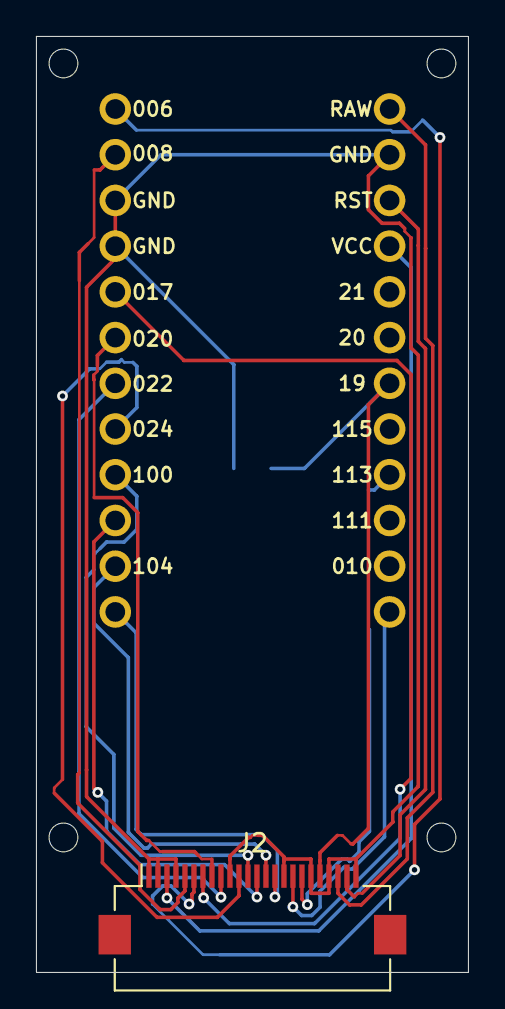
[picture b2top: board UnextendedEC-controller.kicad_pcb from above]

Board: 2 copper layers, 24.0 x 52.0 mm, 7 parts (1 on the bottom side), 17 nets.

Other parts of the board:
MH1, MH2, MH3, MH4: (no value)

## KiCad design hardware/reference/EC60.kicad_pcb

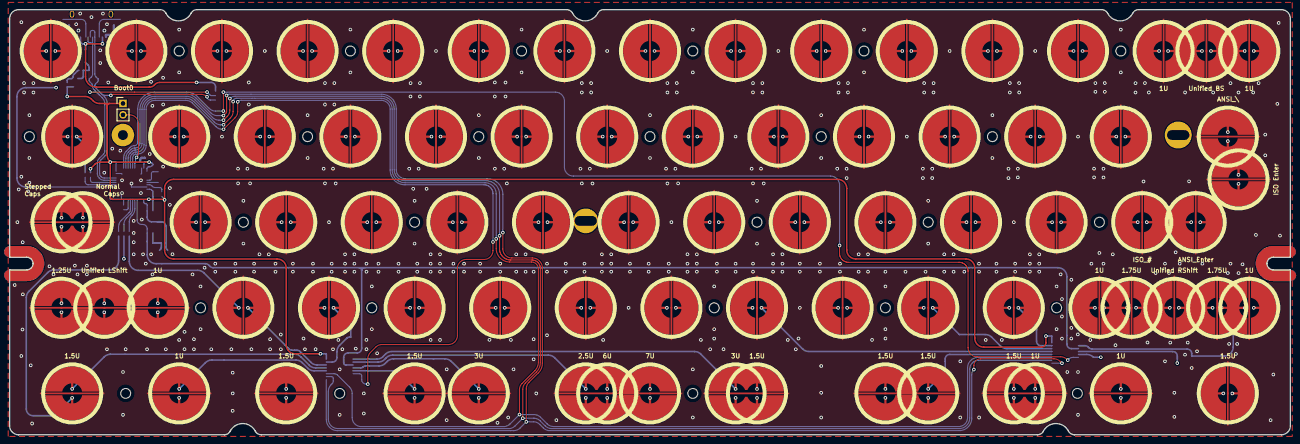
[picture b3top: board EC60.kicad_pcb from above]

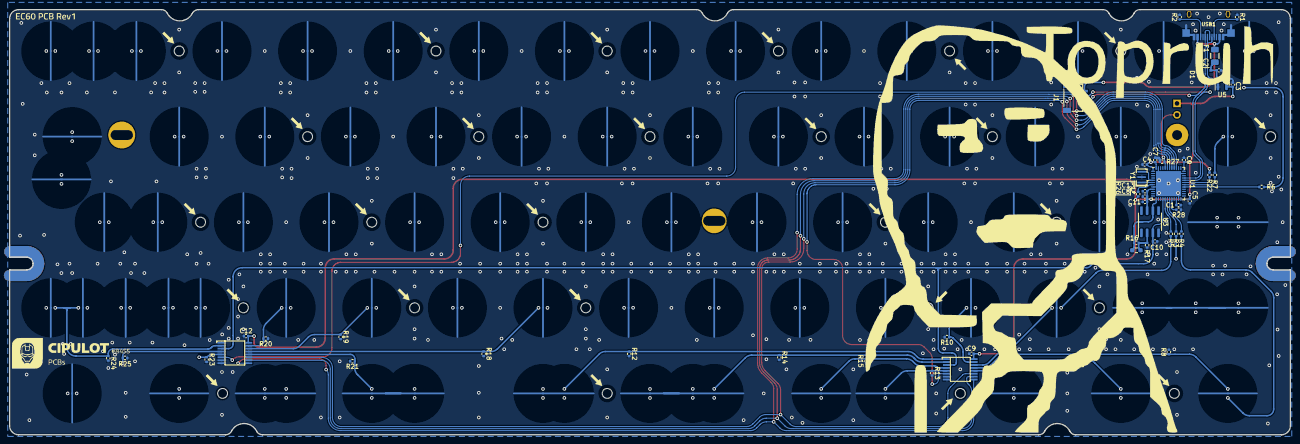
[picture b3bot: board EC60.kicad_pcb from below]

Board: 4 copper layers, 285.0 x 94.6 mm, 153 parts (52 on the bottom side), 48 nets.

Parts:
C1: 4.7u; C_0402_1005Metric
C2, C3, C13: 1u; C_0402_1005Metric
C4, C5, C6, C7, C8, C9, C11, C12: 100n; C_0402_1005Metric
C10: 220p; C_0402_1005Metric
D1: PRTR5V0U2X; SOT-143
F1: 500mA; Fuse_1206_3216Metric
H1, H2, H3, H4, H5, H6, H7, H8, H9, H10, H11, H12, H13, H14, H15, H16, H17, H18, H19, H20, H21, H22, H23, H24, H25, H26: MountingHole; HOLE_M2
J1: JST; JST-SR-4
JP1: Ext_Res; R_0603_1608Metric_Pad0.98x0.95mm_HandSolder
R1, R2: 5.1k; R_0402_1005Metric
R3, R4, R5, R6, R7: 100; R_0402_1005Metric
R8, R9, R10, R11, R12, R13, R14, R15, R16, R18, R19, R20, R21, R22, R23, R24, R25: 100k; R_0402_1005Metric
R17: 1k; R_0402_1005Metric
R26, R27, R28: 10k; R_0402_1005Metric
SW1: BOOT0; PinHeader_1x02_P2.54mm_Vertical
SW2, SW3, SW4, SW5, SW6, SW7, SW8, SW9, SW10, SW11, SW12, SW13, SW14, SW15, SW16, SW17, SW18, SW19, SW20, SW21, SW22, SW23, SW24, SW25, SW26, SW27, SW28, SW29, SW30, SW34, SW35, SW36, SW37, SW38, SW39, SW40, SW41, SW42, SW43, SW44, SW47, SW50, SW51, SW52, SW53, SW54, SW55, SW56, SW57, SW58, SW59, SW61, SW63, SW64, SW65, SW66, SW67, SW70, SW72, SW73, SW74, SW75: EC_SW; ecs_pad_no_ring
SW31: ANSI_\; ecs_pad_no_ring
SW32: ISO_Enter; ecs_pad_no_ring
SW33, SW68, SW69, SW71: EC_SW; ecs_pad_no_ring_stepped&normal
SW45: ISO_|; ecs_pad_no_ring
SW46: ANSI_Enter; ecs_pad_no_ring
SW48, SW49: EC_SW; ecs_pad_no_ring_1u_edge_cut
SW60, SW62: EC_SW_1u&1.75u; ecs_pad_no_ring_1u1.75u
U1: STM32F401CBUx; QFN-48-1EP_7x7mm_P0.5mm_EP5.6x5.6mm
U2, U4: 74HC4051; TSSOP16
U3: OPA350; SOIC-8_3.9x4.9mm_P1.27mm
U5: XC6206PxxxMR; SOT-23
USB1: XUNPU-TYPEC-312DSS-ACP16; XUNPU-TYPEC-312DSS-ACP16-Assembly
Y1: 8 MHz; Resonator_SMD_Murata_CSTxExxV-3Pin_3.0x1.1mm

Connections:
+5V: C2.1, D1.4 (VCC), F1.1, U5.3 (VI)
ADC: JP1.1 (A), R16.1, U1.13 (PA3), U3.6 (OUT)
AMUX_SEL_0: U1.42 (PB6), U2.11 (S0), U4.11 (S0)
AMUX_SEL_1: U1.41 (PB5), U2.10 (S1), U4.10 (S1)
AMUX_SEL_2: U1.40 (PB4), U2.9 (S2), U4.9 (S2)
APLEX_EN_PIN_0: U1.43 (PB7), U2.6 (~E)
APLEX_EN_PIN_1: U1.39 (PB3), U4.6 (~E)
APLEX_OUT_PIN_0: C10.1, U1.16 (PA6), U2.3 (A), U3.3 (IN+), U4.3 (A)
BOOT0: R27.1, SW1.2 (B), U1.44 (BOOT0)
BOOT1: R28.2, U1.20 (PB2)
COL0: R8.1, SW2.1, SW18.1, SW33.1, SW47.2, SW48.1, SW63.1, U2.13 (A0)
COL1: R11.1, SW3.1, SW19.1, SW34.1, SW49.2, SW64.1, U2.12 (A3)
COL2: R9.1, SW4.1, SW20.1, SW35.1, SW50.1, SW65.1, U2.14 (A1)
COL3: R10.1, SW5.1, SW21.1, SW36.1, SW51.1, U2.15 (A2)
COL4: R13.1, SW6.1, SW22.1, SW37.1, SW52.1, SW66.1, U2.5 (A5)
COL5: R15.1, SW7.1, SW23.1, SW38.1, SW53.1, SW67.1, U2.4 (A7)
COL6: R14.1, SW8.1, SW24.1, SW39.1, SW54.1, SW68.1, SW75.1, U2.2 (A6)
COL7: R12.1, SW9.1, SW25.1, SW40.1, SW55.1, SW69.1, U2.1 (A4)
COL8: R18.1, SW10.1, SW26.1, SW41.1, SW56.1, U4.13 (A0)
COL9: R21.1, SW11.1, SW27.1, SW42.1, SW57.1, SW70.1, SW74.1, U4.12 (A3)
COL10: R19.1, SW12.1, SW28.1, SW43.1, SW58.1, SW71.1, U4.14 (A1)
COL11: R20.1, SW13.1, SW29.1, SW44.1, SW59.1, SW72.1, U4.15 (A2)
COL12: R23.1, SW14.1, SW30.1, SW45.1, SW60.1, SW73.1, U4.5 (A5)
COL13: R25.1, SW15.1, SW31.1, SW32.2, SW46.2, SW60.3, SW61.1, U4.4 (A7)
COL14: R24.1, SW16.1, SW17.1, SW62.2, U4.2 (A6)
D+: D1.2 (I/O1), J1.3, U1.33 (PA12), USB1.6 (DP1), USB1.8 (DP2)
D-: D1.3 (I/O2), J1.2, U1.32 (PA11), USB1.5 (DN2), USB1.7 (DN1)
GND: C1.2, C2.2, C3.2, C4.2, C5.2, C6.2, C7.2, C8.2, C9.1, C10.2, C11.1, C12.1, C13.2, D1.1 (GND), J1.4, R1.1, R2.2, R8.2, R9.2, R10.2, R11.2, R12.2, R13.2, R14.2, R15.2, R17.2, R18.2, R19.2, R20.2, R21.2, R23.2, R24.2, R25.2, R27.2, R28.1, SW2.3 (SG), SW3.3 (SG), SW4.3 (SG), SW5.3 (SG), SW6.3 (SG), SW7.3 (SG), SW8.3 (SG), SW9.3 (SG), SW10.3 (SG), SW11.3 (SG), SW12.3 (SG), SW13.3 (SG), SW14.3 (SG), SW15.3 (SG), SW16.3 (SG), SW17.3 (SG), SW18.3 (SG), SW19.3 (SG), SW20.3 (SG), SW21.3 (SG), SW22.3 (SG), SW23.3 (SG), SW24.3 (SG), SW25.3 (SG), SW26.3 (SG), SW27.3 (SG), SW28.3 (SG), SW29.3 (SG), SW30.3 (SG), SW31.3 (SG), SW32.3 (SG), SW33.3 (SG), SW34.3 (SG), SW35.3 (SG), SW36.3 (SG), SW37.3 (SG), SW38.3 (SG), SW39.3 (SG), SW40.3 (SG), SW41.3 (SG), SW42.3 (SG), SW43.3 (SG), SW44.3 (SG), SW45.3 (SG), SW46.3 (SG), SW47.3 (SG), SW48.3 (SG), SW49.3 (SG), SW50.3 (SG), SW51.3 (SG), SW52.3 (SG), SW53.3 (SG), SW54.3 (SG), SW55.3 (SG), SW56.3 (SG), SW57.3 (SG), SW58.3 (SG), SW59.3 (SG), SW60.4 (SG), SW61.3 (SG), SW62.4 (SG), SW63.3 (SG), SW64.3 (SG), SW65.3 (SG), SW66.3 (SG), SW67.3 (SG), SW68.3 (SG), SW69.3 (SG), SW70.3 (SG), SW71.3 (SG), SW72.3 (SG), SW73.3 (SG), SW74.3 (SG), SW75.3 (SG), U1.8 (VSSA), U1.23 (VSS), U1.35 (VSS), U1.47 (VSS), U1.49 (VSS), U2.7 (VEE), U2.8 (GND), U3.4 (V-), U4.1 (A4), U4.7 (VEE), U4.8 (GND), U5.1 (GND), USB1.1 (GND), USB1.12 (GND), USB1.13 (SHIELD), Y1.2
NRST: R26.2, U1.7 (NRST)
unnamed: C1.1, U1.22 (VCAP1)
unnamed: JP1.2 (B), R16.2, R17.1, U3.2 (IN-)
unnamed: R1.2, USB1.4 (CC1)
unnamed: R2.1, USB1.10 (CC2)
unnamed: R3.1, U1.18 (PB0)
unnamed: R4.2, U1.19 (PB1)
unnamed: R5.1, U1.17 (PA7)
unnamed: R6.2, U1.29 (PA8)
unnamed: R7.1, U1.30 (PA9)
unnamed: R22.1, U1.31 (PA10)
ROW0: R6.1, SW2.2, SW3.2, SW4.2, SW5.2, SW6.2, SW7.2, SW8.2, SW9.2, SW10.2, SW11.2, SW12.2, SW13.2, SW14.2, SW15.2, SW16.2, SW17.2
ROW1: R7.2, SW18.2, SW19.2, SW20.2, SW21.2, SW22.2, SW23.2, SW24.2, SW25.2, SW26.2, SW27.2, SW28.2, SW29.2, SW30.2, SW31.2, SW32.1
ROW2: R3.2, SW33.2, SW34.2, SW35.2, SW36.2, SW37.2, SW38.2, SW39.2, SW40.2, SW41.2, SW42.2, SW43.2, SW44.2, SW45.2, SW46.1
ROW3: R5.2, SW47.1, SW48.2, SW49.1, SW50.2, SW51.2, SW52.2, SW53.2, SW54.2, SW55.2, SW56.2, SW57.2, SW58.2, SW59.2, SW60.2, SW62.3
ROW4: R4.1, SW61.2, SW62.1, SW63.2, SW64.2, SW65.2, SW66.2, SW67.2, SW68.2, SW69.2, SW70.2, SW71.2, SW72.2, SW73.2, SW74.2, SW75.2
VBAT: C3.1, C4.1, C5.1, C6.1, C7.1, C8.1, C9.2, C11.2, C12.2, C13.1, R22.2, R26.1, SW1.1 (A), U1.1 (VBAT), U1.9 (VREF+), U1.24 (VDD), U1.36 (VDD), U1.48 (VDD), U2.16 (VCC), U3.7 (V+), U4.16 (VCC), U5.2 (VO)
VBUS: F1.2, J1.1, USB1.2 (VBUS), USB1.11 (VBUS)
XTAL0: U1.5 (PH0), Y1.3
XTAL1: U1.6 (PH1), Y1.1
